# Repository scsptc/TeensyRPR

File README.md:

# TeensyRPR

TeensyRPR is kind of a hobbyist project to keep Robust Packet Radio (RPR) alive.

The project is based on the [Teensy 4.0](https://www.pjrc.com/store/teensy40.html) board and the [Teensy audio shield](https://www.pjrc.com/store/teensy3_audio.html).
It can build completely upon these two modules. You then only need a PTT transistor an some kind of power supply.

The TeensyRPR firmware supports NMEA input and a LC display with ILI9341 controller.

The KiCad directory contains a KiCad project with the complete schematic. The KiCad project goes a step further and removes the need for the Teensy audio shield.

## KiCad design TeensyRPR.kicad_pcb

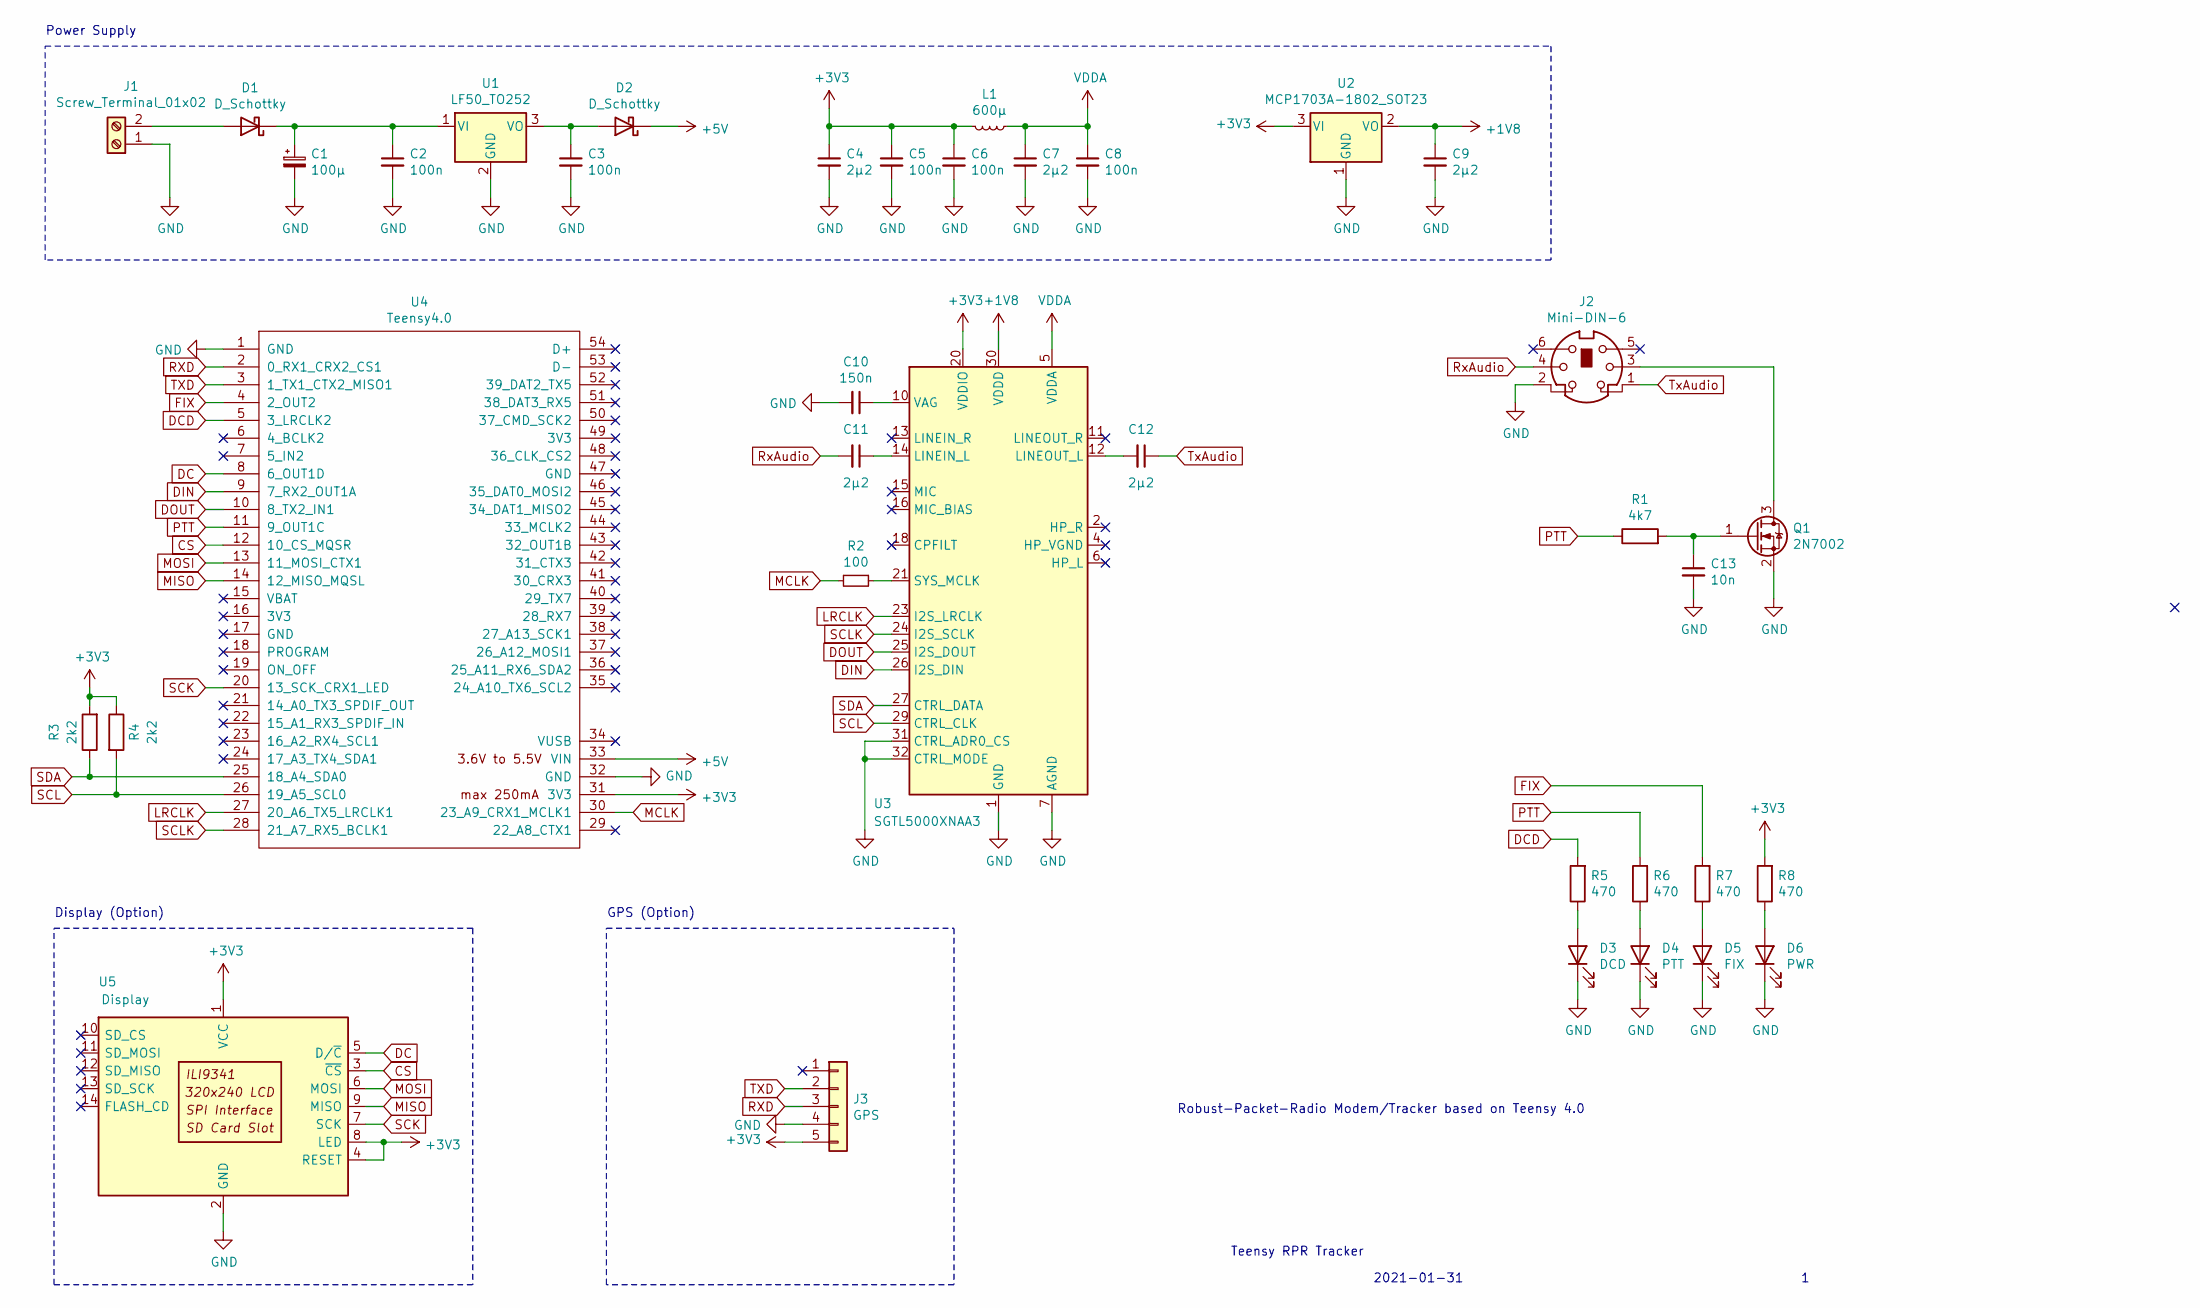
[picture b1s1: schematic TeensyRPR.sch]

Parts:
C1: 100µ; CP_Elec_8x6.5
C2, C3, C5, C6, C8: 100n; C_0805_2012Metric_Pad1.18x1.45mm_HandSolder
C4, C7, C9, C11, C12: 2µ2; C_0805_2012Metric_Pad1.18x1.45mm_HandSolder
C10: 150n; C_0805_2012Metric_Pad1.18x1.45mm_HandSolder
C13: 10n; C_0805_2012Metric_Pad1.18x1.45mm_HandSolder
D1, D2: D_Schottky; D_0402_1005Metric_Pad0.77x0.64mm_HandSolder
D3: DCD; LED_D3.0mm
D4: PTT; LED_D3.0mm
D5: FIX; LED_D3.0mm
D6: PWR; LED_D3.0mm
J1: Screw_Terminal_01x02; TerminalBlock_bornier-2_P5.08mm
J2: Mini-DIN-6; Connector_Mini-DIN_Female_6Pin_2rows
J3: GPS; PinSocket_1x05_P2.54mm_Horizontal
L1: 600µ; L_0805_2012Metric_Pad1.15x1.40mm_HandSolder
Q1: 2N7002; SOT-23
R1: 4k7; R_0805_2012Metric_Pad1.20x1.40mm_HandSolder
R2: 100; R_0805_2012Metric_Pad1.20x1.40mm_HandSolder
R3, R4: 2k2; R_0805_2012Metric_Pad1.20x1.40mm_HandSolder
R5, R6, R7, R8: 470; R_0805_2012Metric_Pad1.20x1.40mm_HandSolder
U1: LF50_TO252; TO-252-2
U2: MCP1703A-1802_SOT23; SOT-23
U3: SGTL5000XNAA3; QFN-32-1EP_5x5mm_P0.5mm_EP3.6x3.6mm
U4: Teensy4.0; Teensy40
U5: Display; CR2013-MI2120

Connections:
+1V8: C9.1, U2.2 (VO), U3.30 (VDDD)
+3V3: C4.1, C5.1, C6.1, J3.5, L1.2, R3.2, R4.1, R8.2, U2.3 (VI), U3.20 (VDDIO), U4.31 (3V3), U5.1 (VCC), U5.4 (RESET), U5.8 (LED)
+5V: D2.1 (K), U4.33 (VIN)
CS: U4.12 (10_CS_MQSR), U5.3 (~CS)
DC: U4.8 (6_OUT1D), U5.5 (D/~C)
DCD: R5.2, U4.5 (3_LRCLK2)
DIN: U3.26 (I2S_DIN), U4.9 (7_RX2_OUT1A)
DOUT: U3.25 (I2S_DOUT), U4.10 (8_TX2_IN1)
FIX: R7.2, U4.4 (2_OUT2)
GND: C1.2, C2.2, C3.2, C4.2, C5.2, C6.2, C7.2, C8.2, C9.2, C10.2, C13.2, D3.1 (K), D4.1 (K), D5.1 (K), D6.1 (K), J1.1, J2.2, J3.4, Q1.2 (S), U1.2 (GND), U2.1 (GND), U3.1 (GND), U3.3 (GND), U3.7 (AGND), U3.31 (CTRL_ADR0_CS), U3.32 (CTRL_MODE), U3.33 (GND), U4.1 (GND), U4.32 (GND), U5.2 (GND)
LRCLK: U3.23 (I2S_LRCLK), U4.27 (20_A6_TX5_LRCLK1)
MCLK: R2.2, U4.30 (23_A9_CRX1_MCLK1)
MISO: U4.14 (12_MISO_MQSL), U5.9 (MISO)
MOSI: U4.13 (11_MOSI_CTX1), U5.6 (MOSI)
unnamed: C1.1, C2.1, D1.1 (K), U1.1 (VI)
unnamed: C3.1, D2.2 (A), U1.3 (VO)
unnamed: C10.1, U3.10 (VAG)
unnamed: C11.1, U3.14 (LINEIN_L)
unnamed: C12.2, U3.12 (LINEOUT_L)
unnamed: C13.1, Q1.1 (G), R1.2
unnamed: D1.2 (A), J1.2
unnamed: D3.2 (A), R5.1
unnamed: D4.2 (A), R6.1
unnamed: D5.2 (A), R7.1
unnamed: D6.2 (A), R8.1
unnamed: J2.3, Q1.3 (D)
unnamed: R2.1, U3.21 (SYS_MCLK)
PTT: R1.1, R6.2, U4.11 (9_OUT1C)
RXD: J3.3, U4.2 (0_RX1_CRX2_CS1)
RxAudio: C11.2, J2.4
SCK: U4.20 (13_SCK_CRX1_LED), U5.7 (SCK)
SCL: R4.2, U3.29 (CTRL_CLK), U4.26 (19_A5_SCL0)
SCLK: U3.24 (I2S_SCLK), U4.28 (21_A7_RX5_BCLK1)
SDA: R3.1, U3.27 (CTRL_DATA), U4.25 (18_A4_SDA0)
TXD: J3.2, U4.3 (1_TX1_CTX2_MISO1)
TxAudio: C12.1, J2.1
VDDA: C7.1, C8.1, L1.1, U3.5 (VDDA)

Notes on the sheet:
Teensy RPR Tracker
2021-01-31
Robust-Packet-Radio Modem/Tracker based on Teensy 4.0
Display (Option)
GPS (Option)
Power Supply

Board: 2 copper layers, 37 parts (0 on the bottom side), 37 nets, no tracks yet.

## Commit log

2021-09-07 Move KiCad files to a separate directory
2021-09-24 Add Apple specific files
2021-09-24 Update schematic PDF
2021-09-24 Add data sheets
